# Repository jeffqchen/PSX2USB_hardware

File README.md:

# PSX2USB_hardware

This is my iteration of a PSX to USB controller adapter. It uses an Arduino Pro Micro as the micro controller. The 3D printed shell packs everything very tight together. Important LEDs shine through hidden windows on the shell.

-------------
## Parts

- [PCB](https://oshpark.com/shared_projects/5XfiUruJ)

- PlayStation Controller Port - [Link](https://github.com/jeffqchen/JeffParts/blob/main/Connectors/PlayStation%20Controller%20Port/info.md)

- Arduino Pro Micro (Preferably 3.3V version) - [Link](https://github.com/jeffqchen/JeffParts/blob/main/Board/Arduino/Pro%20Micro/3.3V%208MHz/info.md)

- [1x] M2x12 Hex screw & nut - [Link](https://github.com/jeffqchen/JeffParts/blob/main/Parts/M2%20M3%20Hex%20Screw%20%26%20Nut/info.md)

- [1x] 0603 size 4.7K SMD resistor

-------------

## Printing

Print the two sides upright with support. That's it.

-------------

## Assembly

Snip off pin 9 flush from the PSX controller plug.

Solder the 4.7K 0603 resistor onto the PCB.

The connection between the Arduino and the PCB is through castellated holes. They are a bit tricky to solder.

Lightly tin both sides of the castellated holes and pads on the PCB before hand. Then, slide the PCB onto the controller plug (mind the orientation, the 4.7K resistor should be visible), then solder the PCB onto the plug, as close as possible to the root of the pins.

Snap the assembly into the 3D-printed plug side part. Put a piece of thin double-sided tape on the exposed side of the plug, then put the Arduino in place.

Then, feed solder into the corresponding holes on the Arduino, while watching when the castelled holes on the PCB start to wet/melt. That indicates the solder has connected. Becareful not to melt the 3D printed shell. Don't heat things up for too long in one go.

Remember to test continuity of these joints with a multimeter before closing up.

-------------

## Software

Find information about the software portion in this repo:
https://github.com/jeffqchen/PSX2USB_software

-------------

Shield: [![CC BY-SA 4.0][cc-by-sa-shield]][cc-by-sa]

This work is licensed under a
[Creative Commons Attribution-ShareAlike 4.0 International License][cc-by-sa].

[![CC BY-SA 4.0][cc-by-sa-image]][cc-by-sa]

[cc-by-sa]: http://creativecommons.org/licenses/by-sa/4.0/
[cc-by-sa-image]: https://licensebuttons.net/l/by-sa/4.0/88x31.png
[cc-by-sa-shield]: https://img.shields.io/badge/License-CC%20BY--SA%204.0-lightgrey.svg

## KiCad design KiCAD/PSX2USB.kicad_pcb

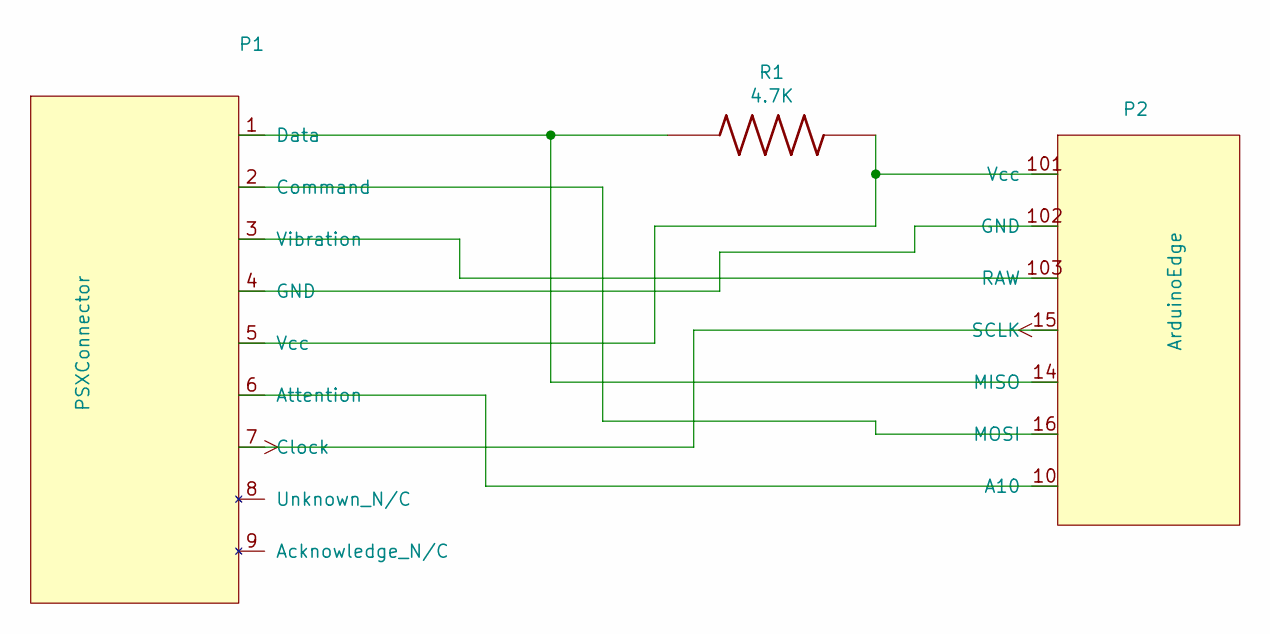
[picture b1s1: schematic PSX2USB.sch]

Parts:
P1: PSXConnector; PSX Controller
P2: ArduinoEdge; Arduino Edge
R1: 4.7K; Resistor

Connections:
unnamed: P1.1 (Data), P2.14 (MISO), R1.1
unnamed: P1.2 (Command), P2.16 (MOSI)
unnamed: P1.3 (Vibration), P2.103 (RAW)
unnamed: P1.4 (GND), P2.102 (GND)
unnamed: P1.5 (Vcc), P2.101 (Vcc), R1.2
unnamed: P1.6 (Attention), P2.10 (A10)
unnamed: P1.7 (Clock), P2.15 (SCLK)

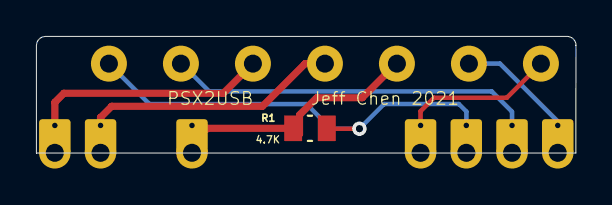
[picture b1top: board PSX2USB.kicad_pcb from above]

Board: 2 copper layers, 30.0 x 6.5 mm, 3 parts (0 on the bottom side), 7 nets.

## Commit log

2021-07-21 First local commit
2022-08-09 Change license type
